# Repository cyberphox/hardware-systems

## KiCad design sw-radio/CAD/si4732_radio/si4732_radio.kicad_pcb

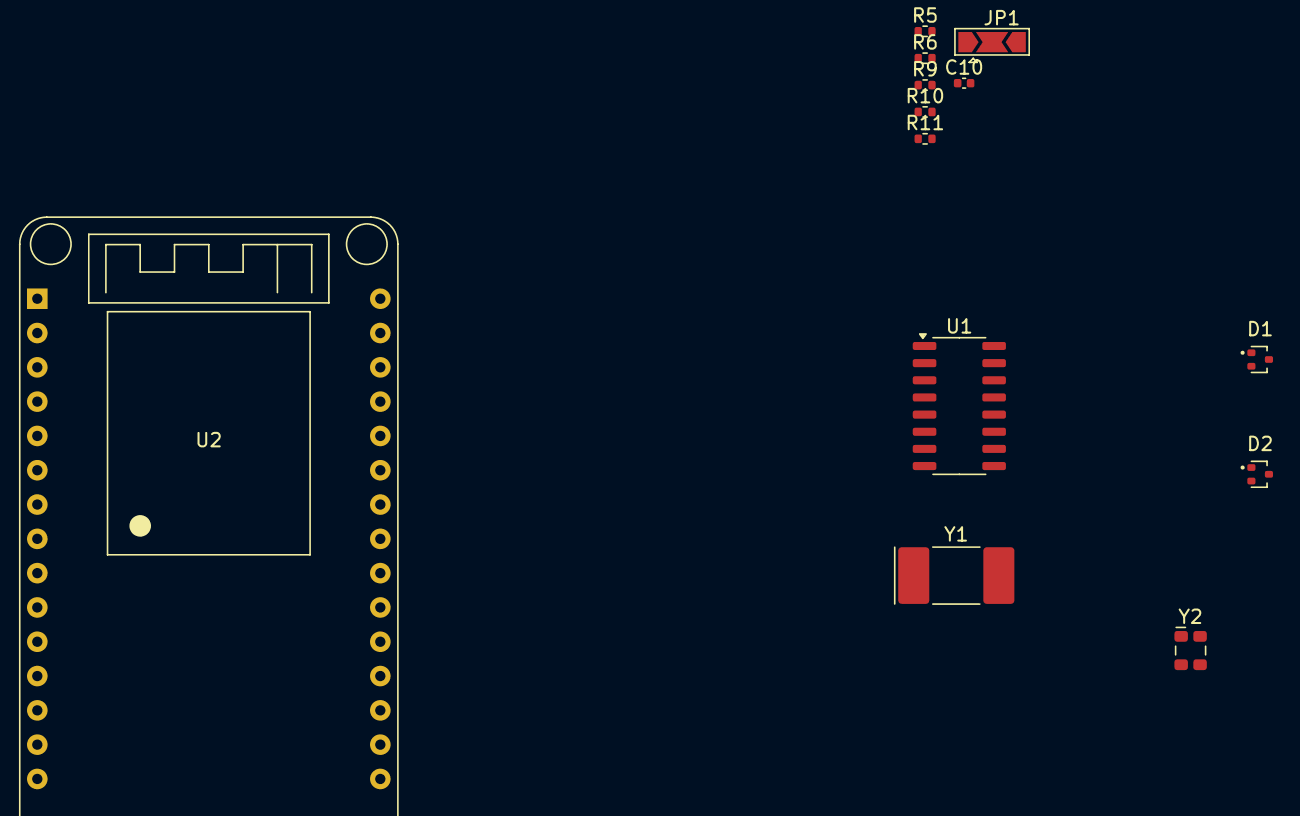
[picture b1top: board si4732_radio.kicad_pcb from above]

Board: 2 copper layers, 13 parts (0 on the bottom side), 10 nets, no tracks yet.

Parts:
C10: 22nF; C_0402_1005Metric
D1, D2: RCLAMP0502B; SOT-416
JP1: Solder 1:2; SolderJumper-3_P2.0mm_Open_TrianglePad1.0x1.5mm
R5, R6: 4K7; R_0402_1005Metric
R9, R10, R11: 0R; R_0402_1005Metric
U1: Si4732-A10-GS; SO-16_3.9x9.9mm_P1.27mm
U2: ESP32_DevKit_V1_DOIT; esp32_devkit_v1_doit
Y1: 32.768KHz; Crystal_SMD_MicroCrystal_CC1V-T1A-2Pin_8.0x3.7mm
Y2: TG2520SMN-32.768Mhz-xxxxNM; Oscillator_SMD_SeikoEpson_TG2520SMN-xxx-xxxxxx-4Pin_2.5x2.0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

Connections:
/radio/GPO3: U1.2 (GPO3/[DCLK]), Y1.1
/radio/RCLK: R9.1, R10.2, U1.13 (RCLK)
/radio/SENB: JP1.2 (C), U1.10 (~SEN)
/radio/VDD_RADIO_3V3: JP1.3 (B), R5.1, R6.1, R11.1, U1.14 (VDD)
/radio/i2c_scl: R6.2, U1.11 (SCLK)
/radio/i2c_sda: R5.2, U1.12 (SDIO)
GND: C10.2, D1.2 (K2), D2.2 (K2), JP1.1 (A), U1.7 (RFGND), U1.15 (GND), U2.14 (GND), U2.17 (GND), Y2.2 (GND)
unnamed: R10.1, Y1.2
unnamed: R9.2, Y2.3 (OUT)
unnamed: C10.1, R11.2, Y2.4 (Vcc)

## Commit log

2026-01-10 initial work
2026-01-10 Further incremental changes
